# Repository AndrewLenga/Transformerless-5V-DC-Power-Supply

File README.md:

⚡ Transformerless 5V DC Power Supply

This repository contains the schematic and design for a Transformerless Linear Power Supply. This circuit uses a Capacitive Dropper instead of a bulky transformer to step down mains voltage, resulting in an extremely compact and lightweight footprint.

⚠️ DANGER: NO GALVANIC ISOLATION ⚠️
This circuit is NOT isolated from the AC mains.

Live Potential: Every component in this circuit, including the DC output terminals, must be considered "Live" at 110V/230V AC.

Safety: Never touch any part of the circuit while it is plugged in. The device must be housed in a fully insulated, non-conductive (plastic) enclosure.

Testing: Use an Isolation Transformer during development to prevent electric shock or damage to your oscilloscope/multimeter.

🔍 Circuit Overview
The design replaces the traditional magnetic transformer with the reactance of a high-voltage capacitor. By using a capacitive voltage divider, the circuit limits the current flowing from the AC mains before rectifying and regulating it.

Key Specifications
Input: 110V/230V AC Mains.
Output: Regulated +5V DC.
Current Capability: Low-current (typically <100mA), determined by the value of C3.
Applications: IoT sensors, LED night lights, and low-power microcontrollers in sealed environments.

🛠️ How It Works

1. The Capacitive Dropper (C3 & R1)
C3 (Reactance): This X2-rated capacitor acts as the "dropper." It provides a high impedance to the 50/60Hz AC signal, effectively stepping down the voltage without the heat generation associated with power resistors.
R1 (Bleeder): A high-value resistor (470kΩ+) connected in parallel to C3. It ensures that when the device is unplugged, the charge stored in C3 is safely discharged.
2. Full-Wave Rectification (D1–D4)
Four 1N4007 diodes arranged in a bridge configuration convert the stepped-down AC into pulsating DC.
3. Filtering & Zener Clamping (C1, D5/D6)
C1 (Filter): Smooths the pulsating DC into a steadier voltage.
D5 & D6 (Zener Diodes): These act as a safety clamp. They prevent the voltage at the input of the regulator from spiking too high, which could happen if the circuit is powered on without a load.
4. Linear Regulation (U1, C2, D8)
U1 (LM7805): Standard linear regulator that provides a precise 5V DC output.
C2 (Stability): A small output capacitor that improves transient response and prevents oscillation.
D8 (Indicator): An LED with a current-limiting resistor (R4) to signal that the power is active.

📊 Component List & Recommendations

Component	Identifier	Recommended Value	Requirement
Dropper Cap	C3	0.47µF - 1µF	X2-Rated (Safety Type)
Bleeder Resistor	R1	470kΩ - 1MΩ	0.5W or higher
Bridge Diodes	D1–D4	1N4007	1A, 1000V Standard
Zener Diodes	D5, D6	12V - 15V	1W Power Rating
Main Regulator	U1	LM7805	TO-220 Package
Filter Cap	C1	470µF - 1000µF	25V or higher

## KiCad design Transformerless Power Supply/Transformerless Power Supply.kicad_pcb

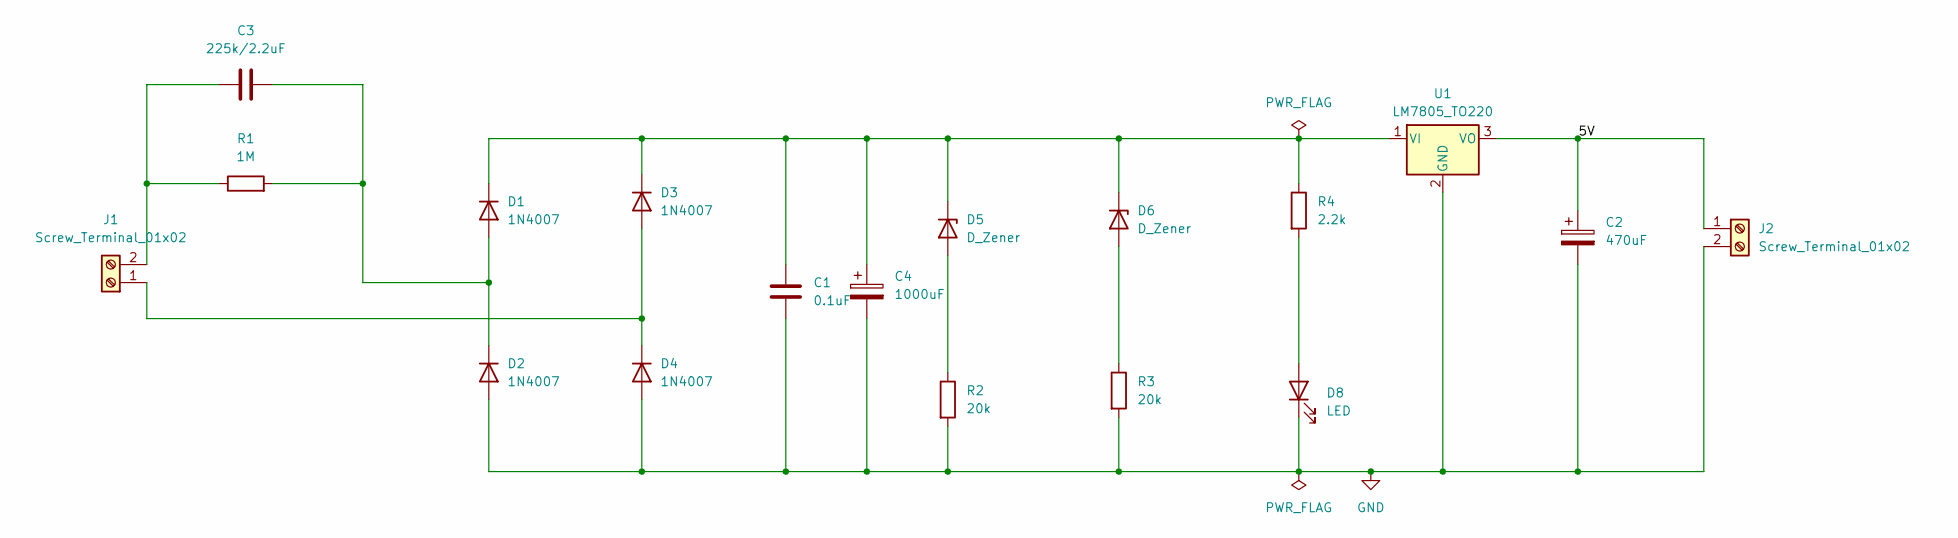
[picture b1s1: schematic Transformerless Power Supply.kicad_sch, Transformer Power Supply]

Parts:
C1: 0.1uF; C_Disc_D4.7mm_W2.5mm_P5.00mm
C2: 470uF; C_Radial_D10.0mm_H12.5mm_P5.00mm
C3: 225k/2.2uF; C_Rect_L7.2mm_W7.2mm_P5.00mm_FKS2_FKP2_MKS2_MKP2
C4: 1000uF; C_Radial_D10.0mm_H12.5mm_P5.00mm
D1, D2, D3, D4: 1N4007; D_DO-41_SOD81_P10.16mm_Horizontal
D5, D6: D_Zener; D_A-405_P7.62mm_Horizontal
D8: LED; LED_D5.0mm
J1, J2: Screw_Terminal_01x02; TerminalBlock_Phoenix_MKDS-1,5-2_1x02_P5.00mm_Horizontal
R1: 1M; R_Axial_DIN0207_L6.3mm_D2.5mm_P10.16mm_Horizontal
R2, R3: 20k; R_Axial_DIN0207_L6.3mm_D2.5mm_P10.16mm_Horizontal
R4: 2.2k; R_Axial_DIN0207_L6.3mm_D2.5mm_P10.16mm_Horizontal
U1: LM7805_TO220; TO-220-3_Vertical

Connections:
GND: C1.2, C2.2, C4.2, D2.2 (A), D4.2 (A), D8.1 (K), J2.2, R2.2, R3.2, U1.2 (GND)
unnamed: C3.2, D1.2 (A), D2.1 (K), R1.2
unnamed: C1.1, C4.1, D1.1 (K), D3.1 (K), D5.1 (K), D6.1 (K), R4.1, U1.1 (VI)
unnamed: D3.2 (A), D4.1 (K), J1.1
unnamed: D5.2 (A), R2.1
unnamed: D6.2 (A), R3.1
unnamed: D8.2 (A), R4.2
unnamed: C3.1, J1.2, R1.1
unnamed: C2.1, J2.1, U1.3 (VO)

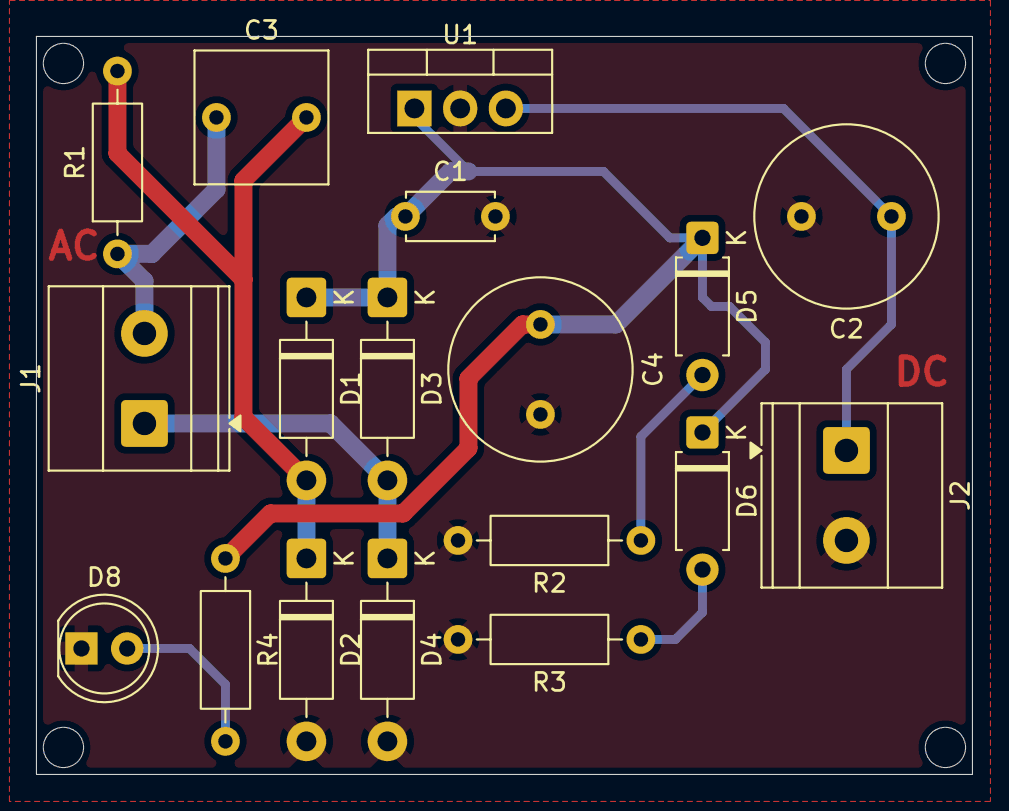
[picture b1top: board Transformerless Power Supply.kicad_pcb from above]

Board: 2 copper layers, 52.0 x 41.0 mm, 18 parts (0 on the bottom side), 9 nets.
